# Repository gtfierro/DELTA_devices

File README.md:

View this project on [CADLAB.io](https://cadlab.io/project/1141). 

# DELTA_devices

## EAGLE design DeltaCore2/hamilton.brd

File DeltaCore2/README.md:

# DELTA Devices

* `DeltaCore2`: the "common" board for all devices

### TODO

- [ ] merge parts list w/ hamilton
- [ ] get the height limitations and decide on the boost's inductor
- [ ] add in analog circuitry for VPCC feedback
- [ ] add control circuitry:
    - [ ] I2C port expander
    - [ ] 2 bulky fets: AON714? (1A)
    - [ ] 4 fets @ 300mA

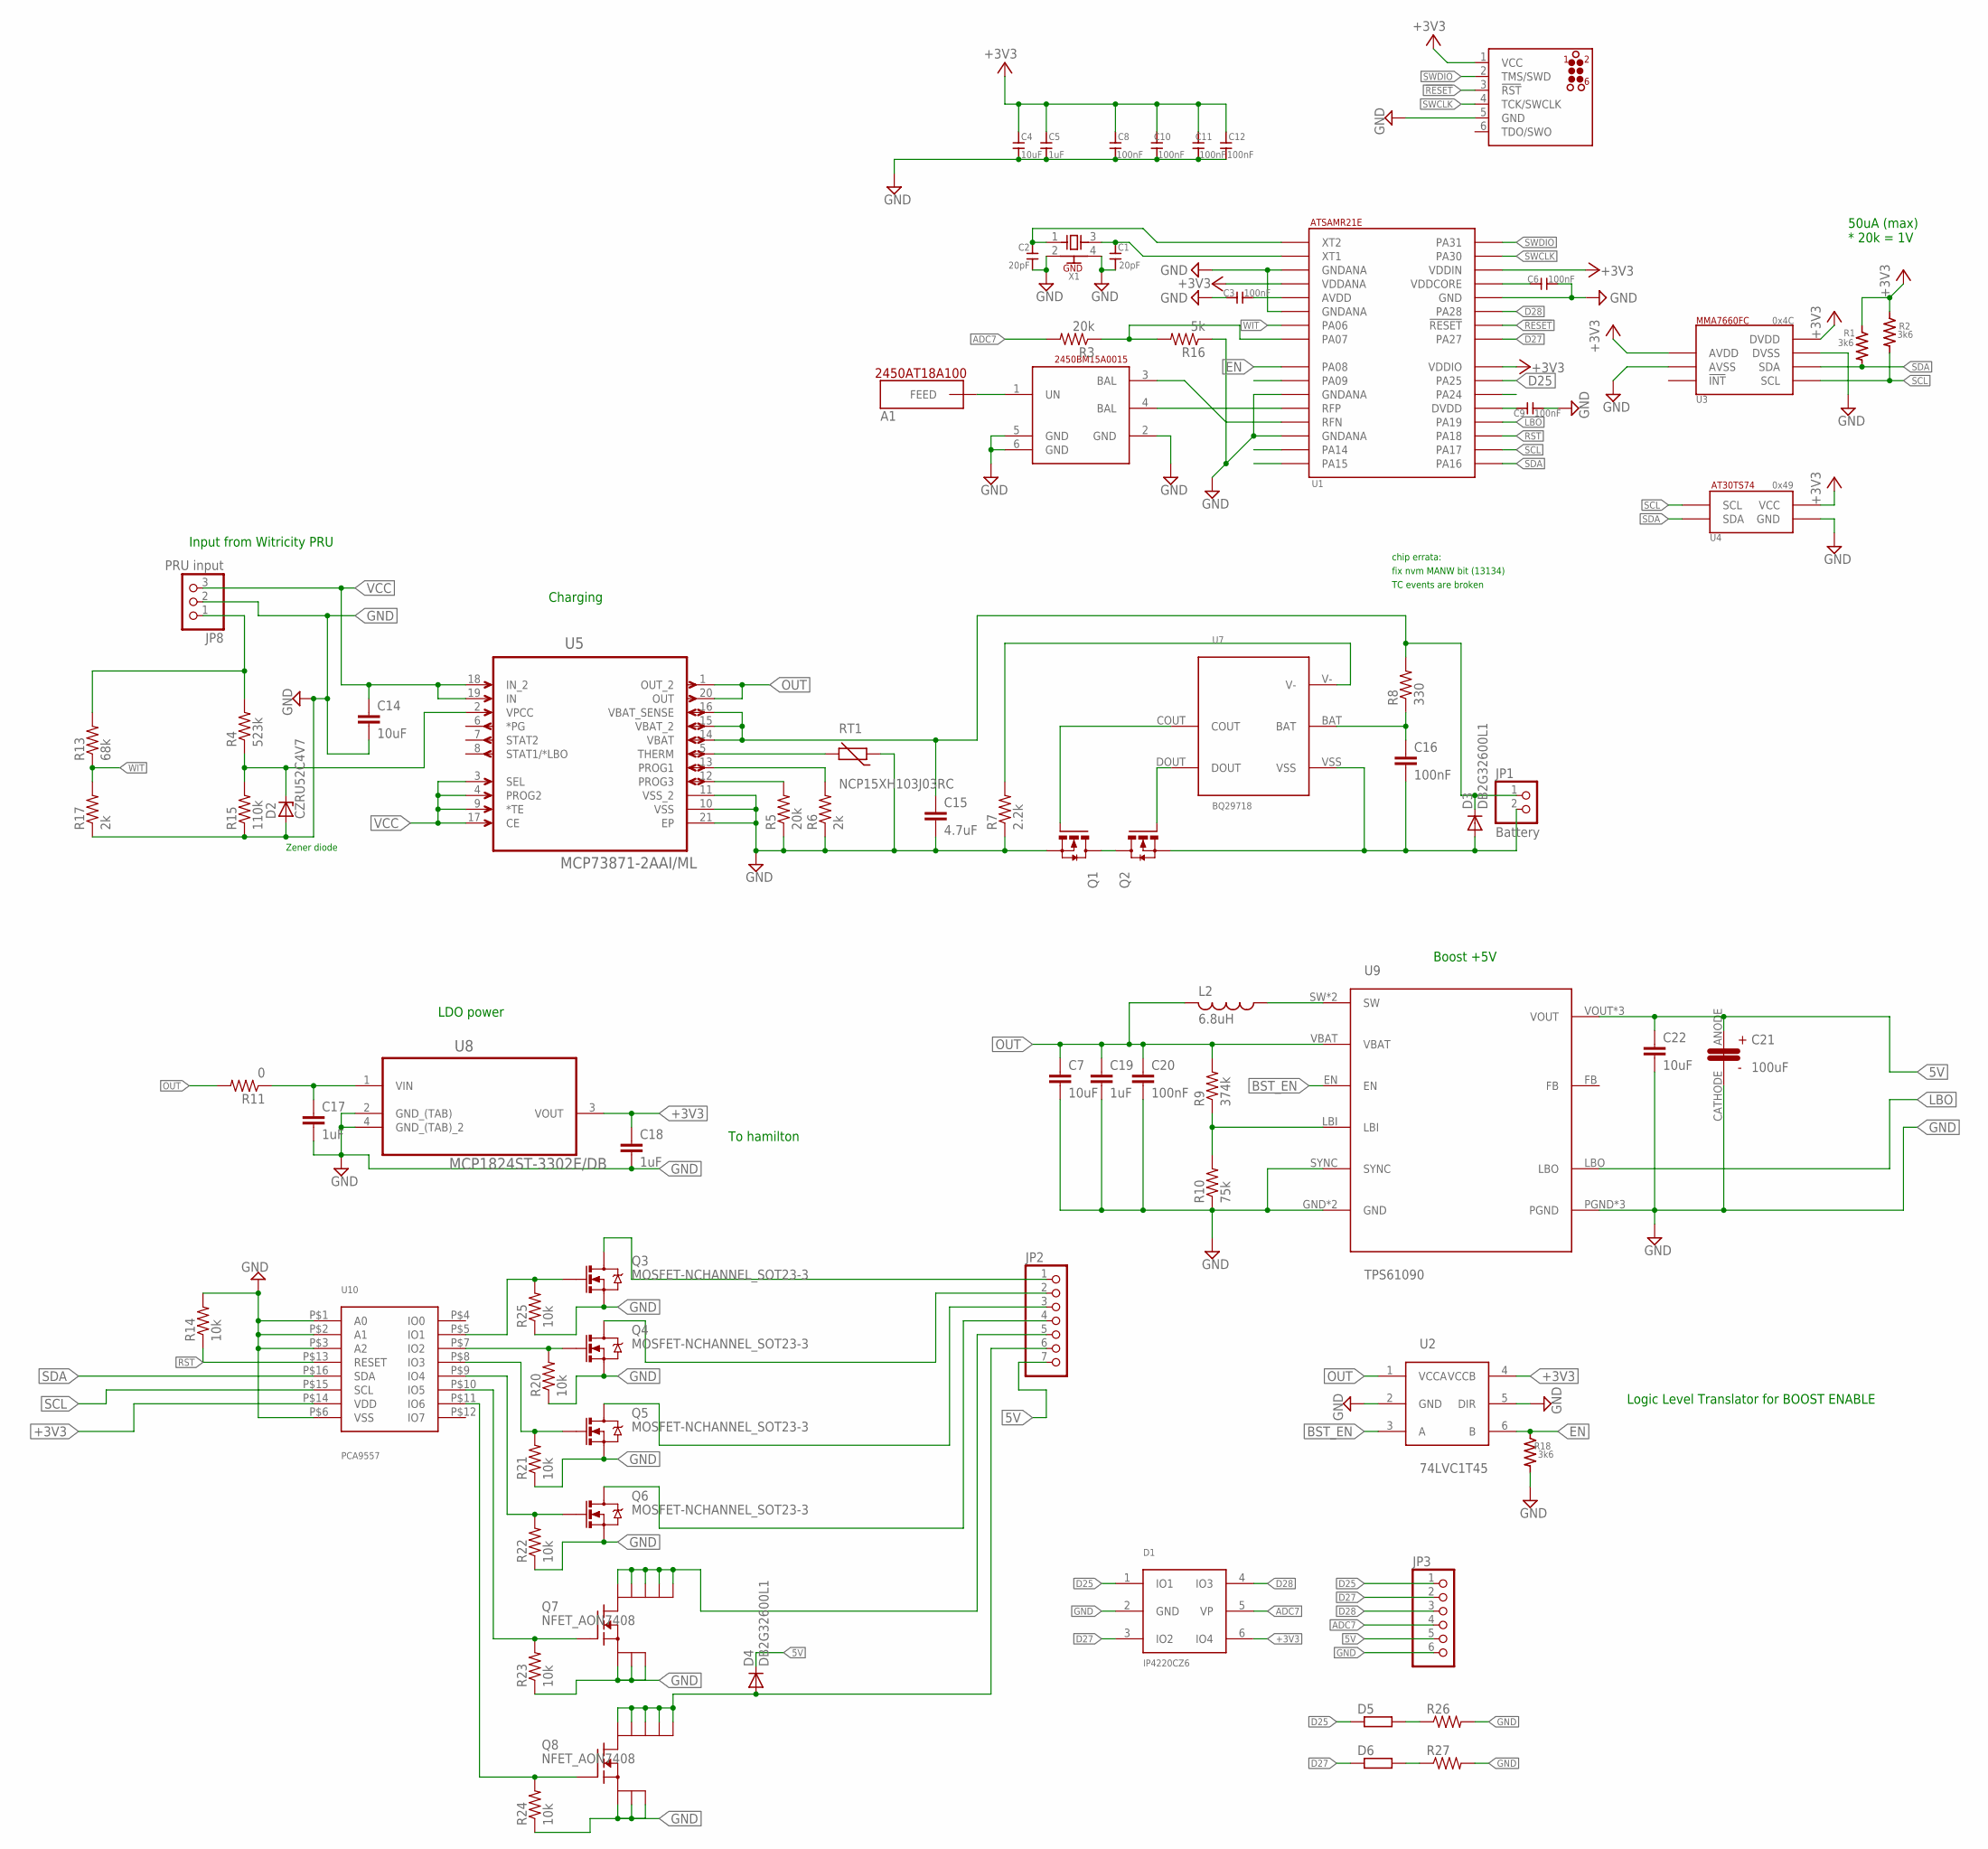
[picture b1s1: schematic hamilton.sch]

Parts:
A1: JOHANSON_ANTENNA2
C1, C2: 20pF; S0402
C3, C6, C8, C9, C10, C11, C12: 100nF; C0402
C4: 10uF; 0805
C5: 1uF; C0402
C7, C14, C22: 10uF; C0603
C15: 4.7uF; C0603
C16, C20: 100nF; C0603
C17, C18, C19: 1uF; C0603
C21: 100uF; 6032
D1: IP4220CZ6; SOT457
D2: CZRU52C4V7; R0603
D3, D4: DB2G32600L1; R0402
D5, D6: R-EU_R0603; R0603
JP1: Battery; 1X02
JP2: PINHD-1X7; 1X07
JP3: PINHD-1X6; 1X06
JP8: PRU input; 1X03
L1: BALUN_JOHANSON
L2: 6.8uH; 2-SMD-7.8-7-5
Q1, Q2: CSD16301Q2; 6-SMD
Q3, Q4, Q5, Q6: MOSFET-NCHANNEL_SOT23-3; SOT23-3
Q7, Q8: NFET_AON7408; VDFN3X38L
R1, R2, R18: 3k6; S0402
R3: 20k; R0402
R4: 523k; R0603
R5: 20k; R0603
R6: 2k; R0603
R7: 2.2k; R0603
R8: 330; R0603
R9: 374k; R0603
R10: 75k; R0603
R11: 0; R0603
R13: 68k; R0402
R14: 10k; R0603
R15: 110k; R0603
R16: 5k; R0402
R17: 2k; R0402
R20, R21, R22, R23, R24, R25: 10k; R0402
R26, R27: R-US_R0402; R0402
RT1: NCP15XH103J03RC; CT/CN0402
U1: SAMR21; QFN32
U2: 74LVC1T45; SOT891
U3: MMA7660FC; MMA7660
U4: AT30TS74; 4WLCSP
U5: MCP73871-2AAI/ML; QFN50P400X400X100-21N
U7: BQ29718; 6-WFDFN
U8: MCP1824ST-3302E/DB; SOT230P700X180-4N
U9: TPS61090; QFN-16
U10: PCA9557; SOT629-1
U$1: JLINK_CONNECT; TC2030-MCP-NL
X1: XTAL

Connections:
5V: C21.ANODE, C22.1, D4.C, JP2.7, JP3.5, U9.VOUT, U9.VOUT_2 (VOUT), U9.VOUT_3 (VOUT)
!RESET!: U1.26 (!RESET!), U$1.3 (!RST!)
+3V3: C4.2, C5.2, C8.1, C10.1, C11.1, C12.1, C18.1, D1.6 (IO4), R1.P$2, R2.P$2, U1.4 (VDDANA), U1.24 (VDDIO), U1.30 (VDDIN), U2.4 (VCCB), U3.3 (AVDD), U3.9 (DVDD), U4.A1 (VCC), U8.3 (VOUT), U10.P$14 (VDD), U$1.1 (VCC)
ADC7: D1.5 (VP), JP3.4, R3.2
BST_EN: U2.3 (A), U9.EN
D25: D1.1 (IO1), D5.1, JP3.1, U1.23 (PA25)
D27: D1.3 (IO2), D6.1, JP3.2, U1.25 (PA27)
D28: D1.4 (IO3), JP3.3, U1.27 (PA28)
EN: R18.P$2, U1.9 (PA08), U2.6 (B)
GND: C1.P$1, C2.P$1, C3.2, C4.1, C5.1, C6.1, C7.2, C8.2, C9.1, C10.2, C11.2, C12.2, C14.2, C15.2, C17.2, C18.2, C19.2, C20.2, C21.CATHODE, C22.2, D1.2 (GND), D2.A, JP3.6, JP8.2, L1.2 (GND), L1.5 (GND), L1.6 (GND), Q1.S_1 (S), Q1.S_2 (S), Q3.2 (S), Q4.2 (S), Q5.2 (S), Q6.2 (S), Q7.1 (S), Q7.2 (S), Q7.3 (S), Q8.1 (S), Q8.2 (S), Q8.3 (S), R5.1, R6.1, R7.1, R10.1, R14.2, R15.1, R16.1, R17.1, R18.P$1, R20.1, R21.1, R22.1, R23.1, R24.1, R25.1, R26.2, R27.2, RT1.1, U1.3 (GNDANA), U1.6 (GNDANA), U1.11 (GNDANA), U1.14 (GNDANA), U1.28 (GND), U2.2 (GND), U2.5 (DIR), U3.4 (AVSS), U3.8 (DVSS), U4.A2 (GND), U5.10 (VSS), U5.11 (VSS_2), U5.21 (EP), U8.2 (GND_(TAB)), U8.4 (GND_(TAB)_2), U9.GND, U9.P$17 (GND), U9.PGND, U9.PGND_2 (PGND), U9.PGND_3 (PGND), U9.SYNC, U10.P$1 (A0), U10.P$2 (A1), U10.P$3 (A2), U10.P$6 (VSS), U$1.5 (GND), X1.2 (GND), X1.4 (GND)
LBO: U1.20 (PA19), U9.LBO
LDOIN: C17.1, R11.1, U8.1 (VIN)
unnamed: JP8.1, R4.2, R13.2
unnamed: L1.3 (BAL), U1.13 (RFN)
unnamed: A1.FEED, L1.1 (UN)
unnamed: C2.P$2, U1.1 (XT2), X1.1 (X1)
unnamed: C6.2, U1.29 (VDDCORE)
unnamed: C3.1, U1.5 (AVDD)
unnamed: C1.P$2, U1.2 (XT1), X1.3 (X2)
unnamed: R3.1, R16.2, U1.8 (PA07)
unnamed: C9.2, U1.21 (DVDD)
unnamed: JP2.5, Q7.5 (D), Q7.6 (D), Q7.7 (D), Q7.8 (D), Q7.PAD (D)
unnamed: L1.4 (BAL), U1.12 (RFP)
unnamed: JP2.1, Q3.3 (D)
unnamed: R5.2, U5.12 (PROG3)
unnamed: R6.2, U5.13 (PROG1)
unnamed: RT1.2, U5.5 (THERM)
unnamed: R7.2, U7.V-
unnamed: C16.1, R8.1, U7.BAT
unnamed: Q1.G, U7.COUT
unnamed: Q2.G, U7.DOUT
unnamed: Q1.D_1 (D), Q1.D_2 (D), Q1.D_3 (D), Q1.D_4 (D), Q1.D_5 (D), Q2.D_1 (D), Q2.D_2 (D), Q2.D_3 (D), Q2.D_4 (D), Q2.D_5 (D)
unnamed: C16.2, D3.A, JP1.2, Q2.S_1 (S), Q2.S_2 (S), U7.VSS
unnamed: D4.A, JP2.6, Q8.5 (D), Q8.6 (D), Q8.7 (D), Q8.8 (D), Q8.PAD (D)
unnamed: L2.P$1 (1), U9.SW, U9.SW_2 (SW)
unnamed: R9.1, R10.2, U9.LBI
unnamed: Q3.1 (G), R25.2, U10.P$5 (IO1)
unnamed: Q4.1 (G), R20.2, U10.P$7 (IO2)
unnamed: Q5.1 (G), R21.2, U10.P$8 (IO3)
unnamed: Q6.1 (G), R22.2, U10.P$9 (IO4)
unnamed: JP2.2, Q4.3 (D)
unnamed: JP2.3, Q5.3 (D)
unnamed: JP2.4, Q6.3 (D)
unnamed: C15.1, D3.C, JP1.1, R8.2, U5.14 (VBAT), U5.15 (VBAT_2), U5.16 (VBAT_SENSE)
unnamed: D5.2, R26.1
unnamed: D6.2, R27.1
unnamed: Q7.4 (G), R23.2, U10.P$10 (IO5)
unnamed: Q8.4 (G), R24.2, U10.P$11 (IO6)
OUT: C7.1, C19.1, C20.1, L2.P$2 (2), R9.2, R11.2, U2.1 (VCCA), U5.1 (OUT_2), U5.20 (OUT), U9.VBAT
RECT: D2.C, R4.1, R15.2, U5.2 (VPCC)
RST: R14.1, U1.19 (PA18), U10.P$13 (RESET)
SCL: R2.P$1, U1.18 (PA17), U3.6 (SCL), U4.B2 (SCL), U10.P$15 (SCL)
SDA: R1.P$1, U1.17 (PA16), U3.7 (SDA), U4.B1 (SDA), U10.P$16 (SDA)
SWCLK: U1.31 (PA30), U$1.4 (TCK/SWCLK)
SWDIO: U1.32 (PA31), U$1.2 (TMS/SWD)
VCC: C14.1, JP8.3, U5.3 (SEL), U5.4 (PROG2), U5.9 (*TE), U5.17 (CE), U5.18 (IN_2), U5.19 (IN)
WIT: R13.1, R17.2, U1.7 (PA06)

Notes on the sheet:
chip errata:
fix nvm MANW bit (13134)
TC events are broken
50uA (max) * 20k = 1V
0x49
0x4C
Input from Witricity PRU
To hamilton
LDO power
Boost +5V
Charging
Logic Level Translator for BOOST ENABLE
Zener diode

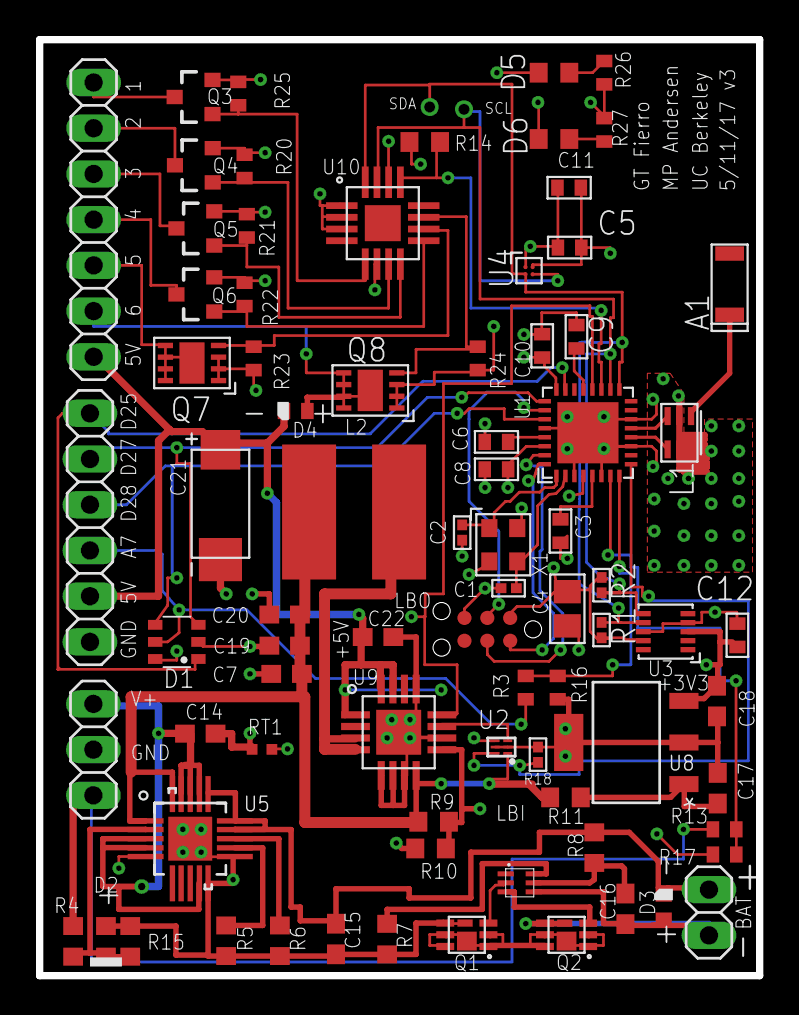
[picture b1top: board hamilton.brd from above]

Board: 4 copper layers, 40.0 x 52.0 mm, 79 parts (0 on the bottom side), 57 nets.

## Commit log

2016-08-16 added power mgmt parts
2016-08-16 adding
2016-08-17 choosing some parts
2016-08-18 adding in fets, i2c expander
2016-08-18 choosing more parts
2016-08-25 more board
2016-08-26 hopefully done routing
2016-08-26 more
2016-08-29 add analog line for fan
2016-08-29 place resistors
2016-08-29 remove TODOs
2016-08-29 todos
2016-08-30 fixes
2016-08-31 move i2c out from under inductor
2016-09-25 latest updates
2016-11-09 next version
2017-04-28 adding next version of board
2017-08-31 Create LICENSE
2018-06-07 Backlink to CADLAB.io has been added.

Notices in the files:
parts and their libraries:
storm: ©2009 ROFA.cz
